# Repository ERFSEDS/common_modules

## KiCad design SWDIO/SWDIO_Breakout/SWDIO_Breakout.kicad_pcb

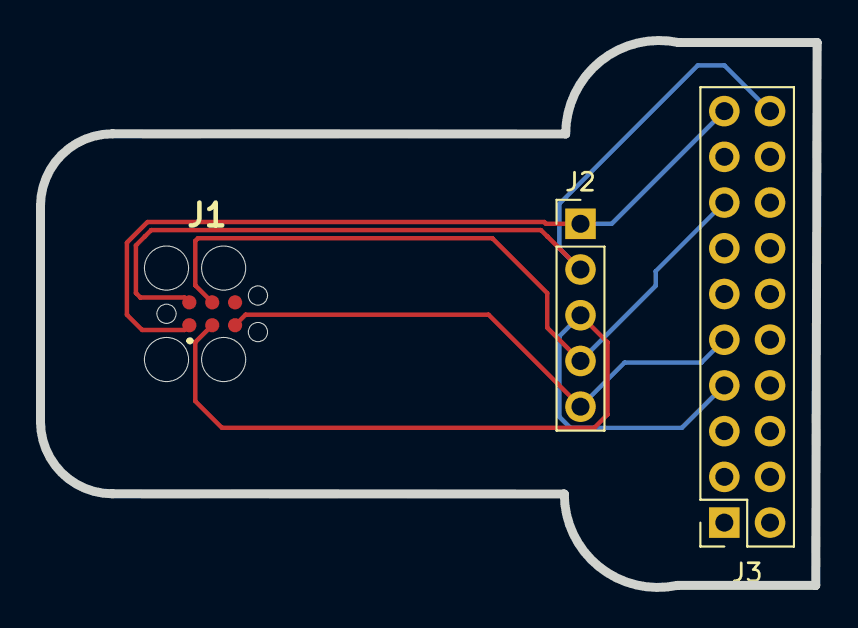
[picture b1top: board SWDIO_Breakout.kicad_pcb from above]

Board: 2 copper layers, 43.1 x 30.4 mm, 3 parts (0 on the bottom side), 5 nets.

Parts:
J1: 8.06.16; 80616
J2: Conn_01x05_Male; PinHeader_1x05_P2.54mm_Vertical
J3: Conn_01x20_Male; PinSocket_2x10_P2.54mm_Vertical

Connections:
+3.3V: J1.1, J2.1, J3.19
GND: J1.2, J2.2, J3.20
RESET: J1.4, J2.4, J3.15
SWCLK: J1.5, J2.5, J3.9
SWDIO: J1.3, J2.3, J3.7

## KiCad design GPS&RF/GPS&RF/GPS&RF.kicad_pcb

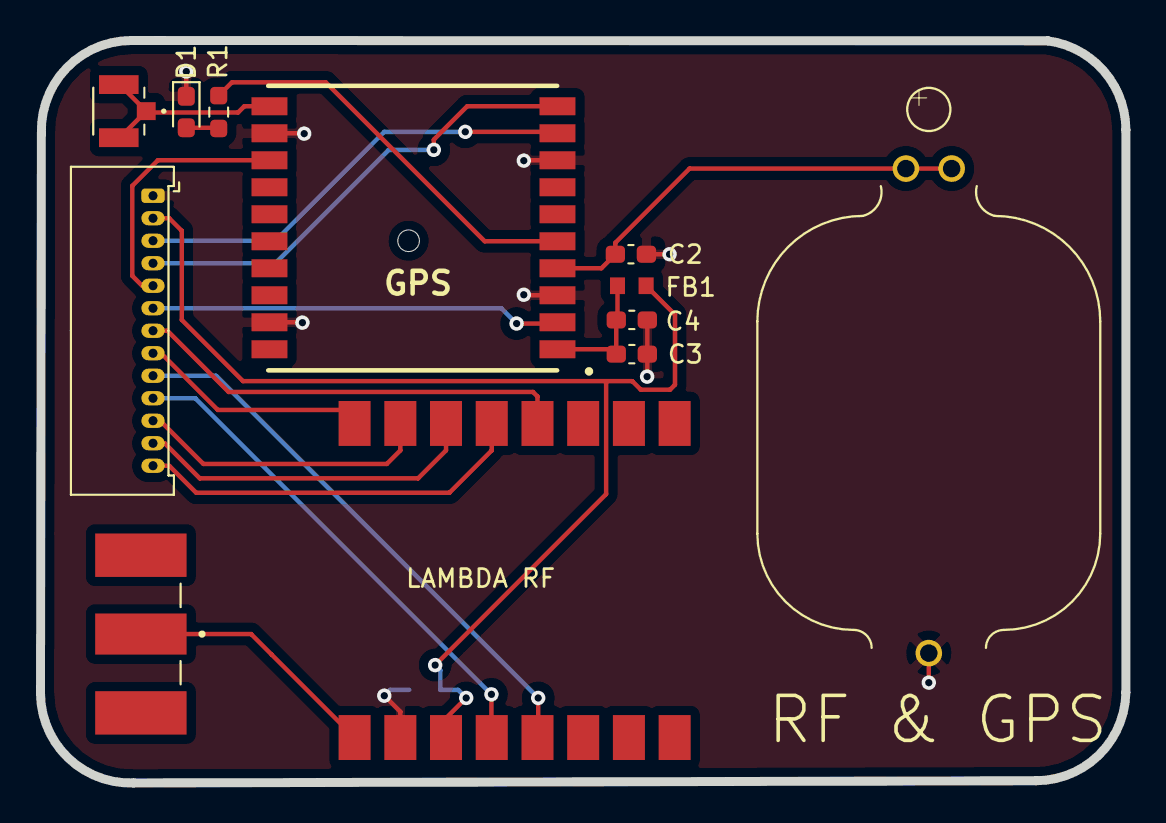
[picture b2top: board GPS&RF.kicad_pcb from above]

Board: 2 copper layers, 60.3 x 41.2 mm, 13 parts (1 on the bottom side), 19 nets.

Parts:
 : Conn_01x13_Male; Molex_PicoBlade_53048-1310_1x13_P1.25mm_Horizontal
 #2: U.FL-R-SMT(10); HRS_U.FL-R-SMT(10)
 #3: BATT; BAT_120591-1
 #4: Antenna; CINCH_142-0701-801
 LAMBDA RF: LAMBDA-9S-Global; LAMBDA-9S
C1: 100nF; C_0603_1608Metric_Pad1.08x0.95mm_HandSolder
C2, C3: 1uF; C_0603_1608Metric_Pad1.08x0.95mm_HandSolder
C4: 0.01uF; C_0603_1608Metric_Pad1.08x0.95mm_HandSolder
D1: LED; LED_0603_1608Metric_Pad1.05x0.95mm_HandSolder
FB1: Ferrite_Bead; BEADC1608X90N
GPS: FGPMMOPA6H
R1: 330ohm; R_0603_1608Metric_Pad0.98x0.95mm_HandSolder

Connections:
+3V3: .2, LAMBDA RF.3, C1.2, FB1.2
/1PPS: .5, GPS.13
/CS: .8, LAMBDA RF.16
/GPSRST: .6, GPS.2
/MISO: .12, LAMBDA RF.14
/MOSI: .11, LAMBDA RF.15
/RFRST: .7, LAMBDA RF.12
/RX_D1: .9, LAMBDA RF.5
/RX_D2: .3, GPS.9
/SCK: .13, LAMBDA RF.13
/TX_D1: .10, LAMBDA RF.4
/TX_D2: .4, GPS.10
GND: .1, #3.-, LAMBDA RF.2, C1.1, C2.2, C3.1, C4.1, D1.1, GPS.3, GPS.8, GPS.12, GPS.19
unnamed: #4.1, LAMBDA RF.1
unnamed: #3.+1, #3.+2, C2.1, GPS.4
unnamed: C3.2, C4.2, FB1.1, GPS.1
unnamed: D1.2, R1.2
unnamed: GPS.5, R1.1
unnamed: #2.1, #2.2, #2.3, GPS.11

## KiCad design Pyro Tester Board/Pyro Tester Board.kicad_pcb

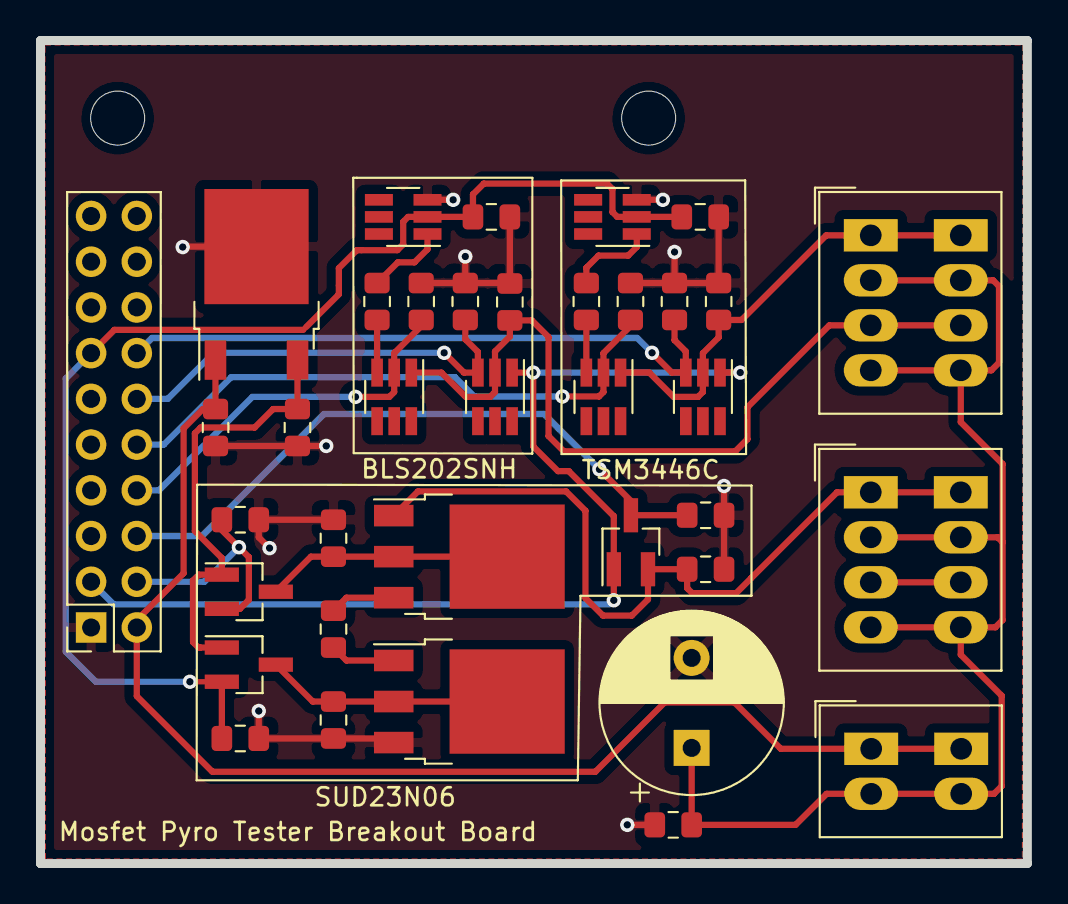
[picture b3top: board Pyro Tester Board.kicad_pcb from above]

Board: 2 copper layers, 54.8 x 45.7 mm, 39 parts (0 on the bottom side), 23 nets.

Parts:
C1: 1mF; CP_Radial_D10.0mm_P5.00mm
C2: 0.33uF; C_0805_2012Metric_Pad1.15x1.40mm_HandSolder
C3: 01.uF; C_0805_2012Metric_Pad1.15x1.40mm_HandSolder
H1, H2: MountingHole; MountingHole_3mm
J1: Conn_02x10_Counter_Clockwise; PinSocket_2x10_P2.54mm_Vertical
J2: Conn_01x02_Female; TerminalBlock_Phoenix_PTSM-0,5-2-2.5-H-THR_1x02_P2.50mm_Hor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
J3, J4: Conn_01x04_Female; TerminalBlock_Phoenix_PTSM-0,5-4-2.5-H-THR_1x04_P2.50mm_Hor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
Q1, Q2, Q3, Q4, Q5, Q6: Q_NJFET_DGS; SOT-23-6_Handsoldering
Q7, Q8, Q11: Q_NJFET_DGS; SOT-23_Handsoldering
Q9, Q10: Q_NJFET_DGS; TO-252-3_TabPin2
R1, R2, R3, R5, R6, R7, R9, R10, R11, R12, R13, R14, R16, R17, R18: 10k; R_0805_2012Metric_Pad1.15x1.40mm_HandSolder
R4, R8, R15: 3.3; R_0805_2012Metric_Pad1.15x1.40mm_HandSolder
U1: LM78M05_TO252; TO-252-2

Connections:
+3V3: J1.3, Q3.1, Q6.1, Q11.1
+5V: C3.1, Q7.1, Q8.1, U1.3
+BATT: C2.1, J1.2, J2.1, U1.1
/Arm: J1.13, Q2.2, Q5.2, Q8.2, R1.1, R12.1, R18.1
/Continuity1: J1.14, Q3.3, R10.1
/Continuity2: J1.12, Q6.3, R6.1
/Continuity3: J1.6, Q11.3, R17.1
/Fire1: J1.10, Q1.2, R7.1
/Fire2: J1.8, Q4.2, R3.1
/Fire3: J1.4, Q7.2, R11.1
/Pyro1: J3.1, Q1.1, Q3.2, R9.1
/Pyro2: J3.3, Q4.1, Q6.2, R5.1
/Pyro3: J4.1, Q9.1, Q11.2, R16.1
GND: C1.2, C2.2, C3.2, J1.1, Q2.3, Q5.3, Q10.3, R1.2, R2.2, R3.2, R5.2, R6.2, R7.2, R9.2, R10.2, R11.2, R12.2, R13.2, R14.2, R16.2, R17.2, R18.2, U1.2
unnamed: C1.1, J2.2, J3.2, J3.4, J4.2, J4.4, R2.1
unnamed: Q1.3, R8.1
unnamed: Q2.1, R8.2
unnamed: Q4.3, R4.1
unnamed: Q5.1, R4.2
unnamed: Q7.3, Q9.2, R13.1
unnamed: Q9.3, R15.1
unnamed: Q10.1, R15.2
unnamed: Q8.3, Q10.2, R14.1

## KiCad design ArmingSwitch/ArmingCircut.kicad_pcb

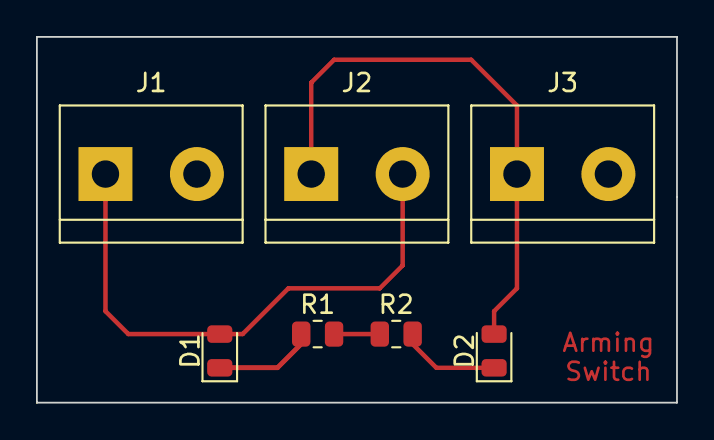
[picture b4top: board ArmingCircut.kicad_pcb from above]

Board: 2 copper layers, 35.6 x 20.3 mm, 7 parts (0 on the bottom side), 5 nets.

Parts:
D1, D2: LED; LED_0805_2012Metric
J1, J2, J3: Screw_Terminal_01x02; TerminalBlock_bornier-2_P5.08mm
R1, R2: R; R_0805_2012Metric

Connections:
GND: R1.2, R2.1
unnamed: D1.1, R1.1
unnamed: D1.2, J1.1, J2.2
unnamed: D2.1, R2.2
unnamed: D2.2, J2.1, J3.1

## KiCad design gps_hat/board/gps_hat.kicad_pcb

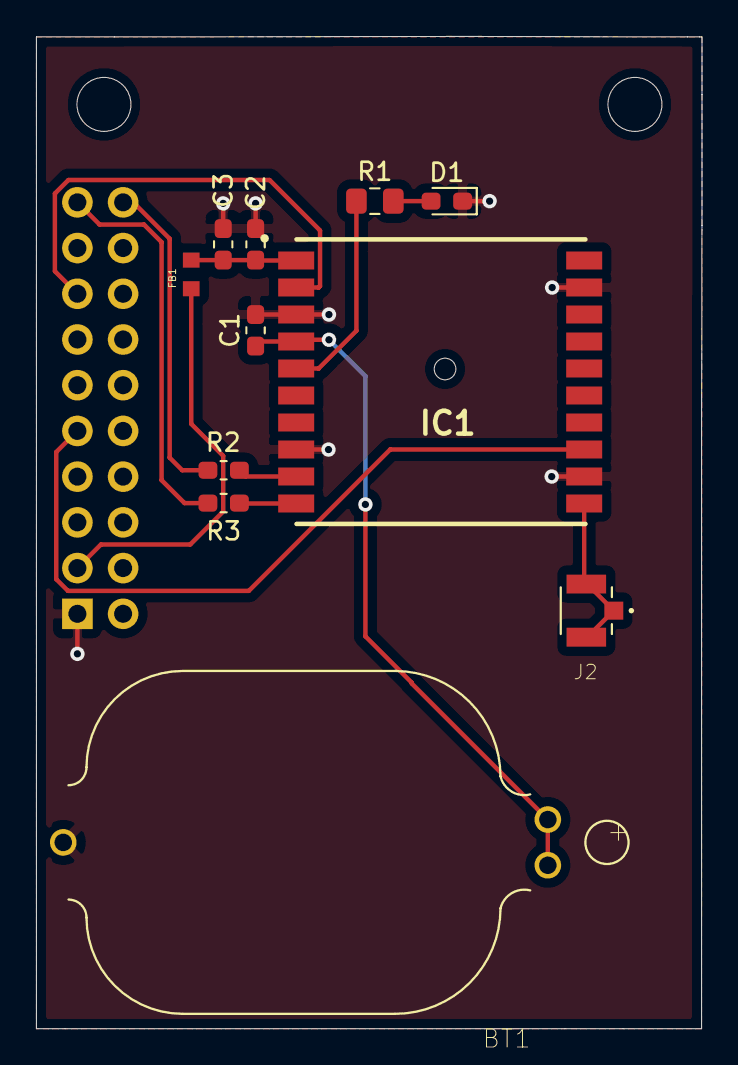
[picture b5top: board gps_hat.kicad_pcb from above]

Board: 2 copper layers, 37.0 x 55.1 mm, 14 parts (1 on the bottom side), 13 nets.

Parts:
 : MountingHole; MountingHole_3mm
 #2: MountingHole; MountingHole_3mm
BT1: BATT; BAT_120591-1
C1, C2: 1uF; C_0603_1608Metric_Pad1.05x0.95mm_HandSolder
C3: 0.01uF; C_0603_1608Metric_Pad1.05x0.95mm_HandSolder
D1: LED; LED_0603_1608Metric_Pad1.05x0.95mm_HandSolder
FB1: 600 Ohm; BEADC1608X90N
IC1: MTK3339; FGPMMOPA6H
J1: Conn_02x10_Odd_Even; PinHeader_2x10_P2.54mm_Vertical
J2: U.FL-R-SMT(10); HRS_U.FL-R-SMT(10)
R1: 330ohm; R_0805_2012Metric_Pad1.15x1.40mm_HandSolder
R2, R3: 330ohm; R_0603_1608Metric_Pad1.05x0.95mm_HandSolder

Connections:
+3V3: FB1.1, J1.3
/1PPS: IC1.13, J1.9
/NRESET: IC1.2, J1.15
/RX: J1.20, R2.2
/TX: J1.19, R3.2
GND: BT1.-, C1.2, C2.1, C3.1, D1.1, IC1.3, IC1.8, IC1.12, IC1.19, J1.1
unnamed: BT1.+1, BT1.+2, C1.1, IC1.4
unnamed: C2.2, C3.2, FB1.2, IC1.1
unnamed: D1.2, R1.2
unnamed: IC1.5, R1.1
unnamed: IC1.9, R2.1
unnamed: IC1.10, R3.1
unnamed: IC1.11, J2.1, J2.2, J2.3

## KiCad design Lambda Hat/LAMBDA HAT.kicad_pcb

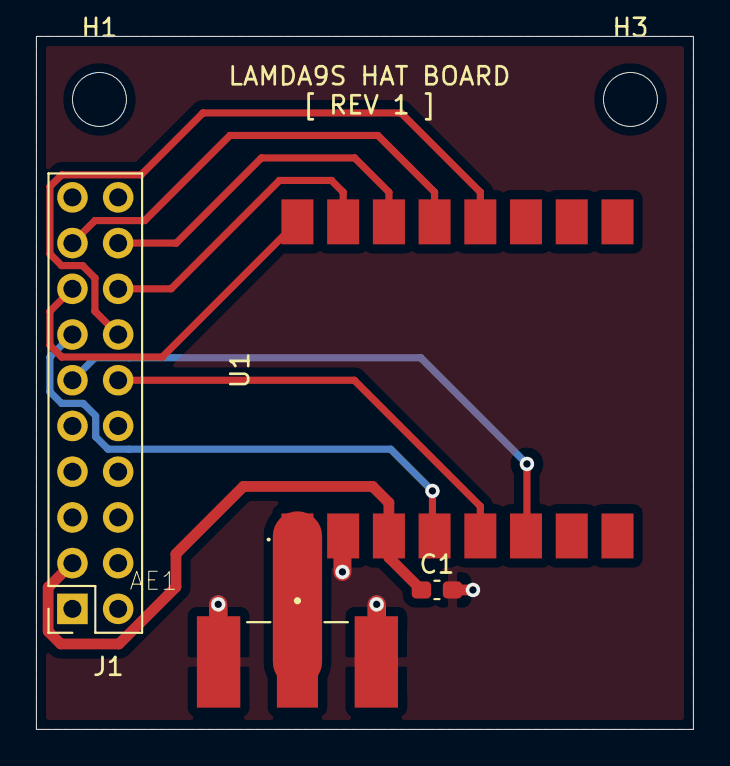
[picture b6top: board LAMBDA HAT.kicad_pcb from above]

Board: 2 copper layers, 36.5 x 38.5 mm, 6 parts (0 on the bottom side), 11 nets.

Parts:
AE1: Antenna; CINCH_142-0701-801
C1: 100n; C_0603_1608Metric_Pad1.08x0.95mm_HandSolder
H1, H3: MountingHole; MountingHole_3mm
J1: Conn_02x10_Counter_Clockwise; PinHeader_2x10_P2.54mm_Vertical
U1: LAMBDA-9S-Global; LAMBDA-9S

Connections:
+3V3: C1.1, J1.3, U1.3
/DIO: J1.11, U1.6
/MISO: J1.18, U1.14
/MOSI: J1.16, U1.15
/RESET: J1.14, U1.12
/RX_SWITCH: J1.13, U1.4
/SCK: J1.17, U1.13
/TX_SWITCH: J1.12, U1.5
/nCS: J1.15, U1.16
GND: AE1.S1, AE1.S2, AE1.S3, AE1.S4, C1.2, J1.1, U1.2
unnamed: AE1.1, U1.1

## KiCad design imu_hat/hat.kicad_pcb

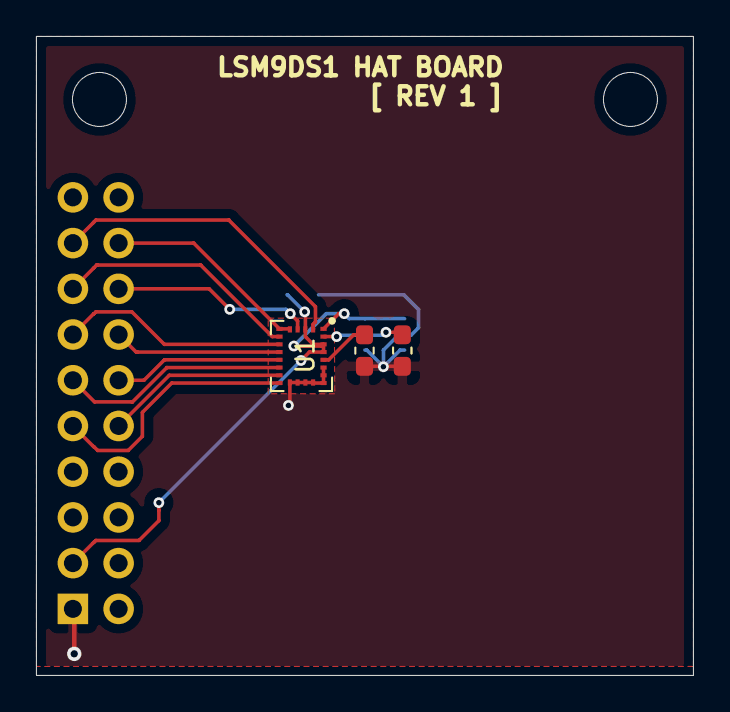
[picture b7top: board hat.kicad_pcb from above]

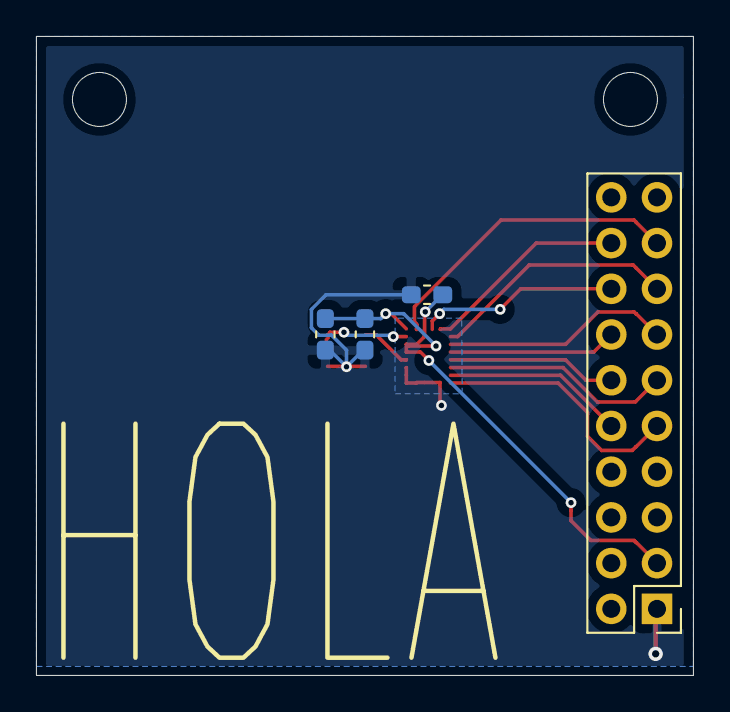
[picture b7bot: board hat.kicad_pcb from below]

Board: 2 copper layers, 36.5 x 35.5 mm, 9 parts (4 on the bottom side), 14 nets.

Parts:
C1: 10nF; C_0603_1608Metric_Pad1.05x0.95mm_HandSolder
C2, C3, C4: 100nF; C_0603_1608Metric_Pad1.05x0.95mm_HandSolder
C5: 10uF; C_0603_1608Metric_Pad1.05x0.95mm_HandSolder
H1, H3: MountingHole; MountingHole_3mm
J1: Conn_02x10_Odd_Even; PinHeader_2x10_P2.54mm_Vertical
U1: LSM9DS1; LGA-24L_3x3.5mm_P0.43mm

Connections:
+3V3: C2.1, C4.1, C5.1, J1.3, U1.1, U1.3, U1.22, U1.23
/CS: J1.15, U1.7
/CSM: J1.13, U1.8
/DEN: J1.9, U1.13
/DRDYM: J1.14, U1.9
/INT1: J1.11, U1.11
/INT2: J1.10, U1.12
/INTM: J1.12, U1.10
/MISO: J1.18, U1.5, U1.6
/MOSI: J1.16, U1.4
/SCLK: J1.17, U1.2
GND: C1.2, C2.2, C3.2, C4.2, C5.2, J1.1, U1.14, U1.15, U1.16, U1.17, U1.18, U1.19, U1.20
unnamed: C1.1, U1.21
unnamed: C3.1, U1.24

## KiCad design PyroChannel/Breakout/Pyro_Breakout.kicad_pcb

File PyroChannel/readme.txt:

This circuit is broken up into 2 sheets, an arming sheet, which each board
only needs one, then a pyro channel, which can have as many as desired
This circuit also allows for the pyro channel to be checked

The maximum voltage that this circuit can take is 12V, at which point the
transistors will break down. THe maximum current the transistors can
sustain is 5 amps continuous or 25 for a pulse

to fire a channel n
	digitalWrite(armPin, HIGH)
	digitalWite(channelNPin, HIGH)

to check if channel n is armed
	digitalRead(channelNPyro)

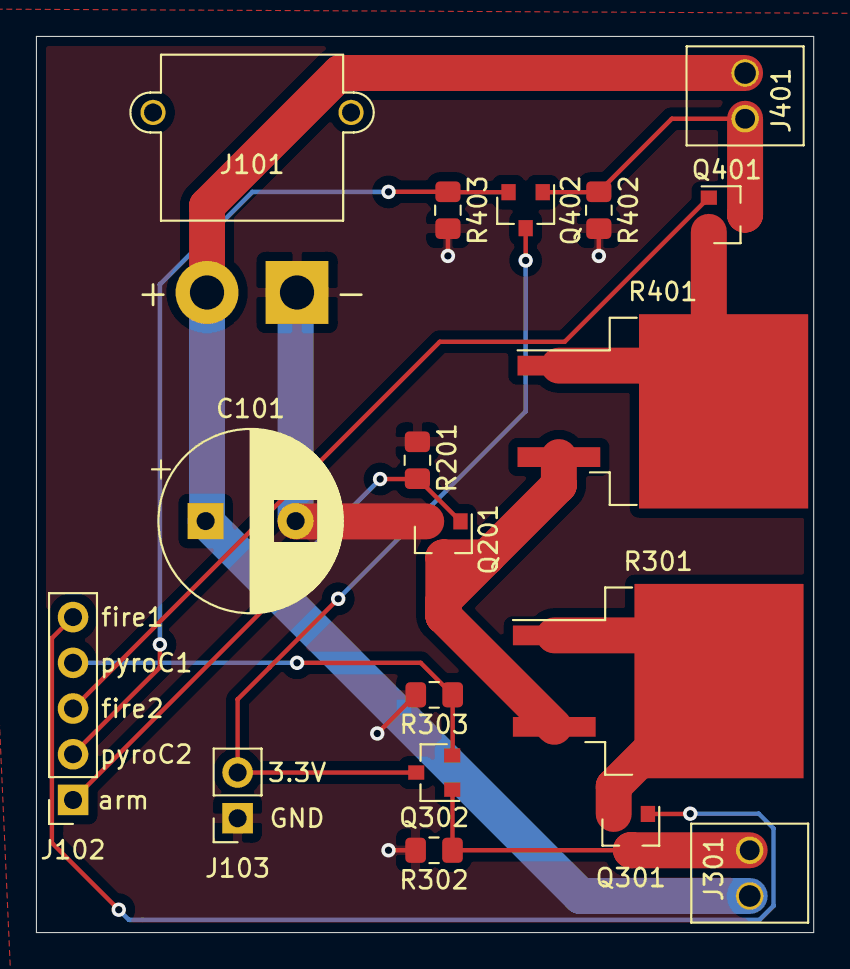
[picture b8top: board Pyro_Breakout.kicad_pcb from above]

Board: 2 copper layers, 43.2 x 49.8 mm, 18 parts (0 on the bottom side), 13 nets.

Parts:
C101: 1mF; CP_Radial_D10.0mm_P5.00mm
J101: Conn_01x02; AMASS_XT30PW-M_1x02_P2.50mm_Horizontal
J102: Conn_01x05; PinSocket_1x05_P2.54mm_Vertical
J103: Conn_01x02; PinSocket_1x02_P2.54mm_Vertical
J301, J401: Conn_01x02_Female; 2_pin_screw_terminal
Q201, Q301, Q302, Q401, Q402: IRLML6344TRPBFee; SOT-23
R201, R302, R303, R402, R403: 10k; R_0805_2012Metric_Pad1.15x1.40mm_HandSolder
R301, R401: 3.3; TO-263-2_TabPin1

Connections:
+3V3: J103.2, Q302.3, Q402.3
+BATT: C101.1, J101.2, J301.1, J401.1
/ArmSchematic/FireOut: Q201.3, R301.2, R401.2
/arm: J102.1, Q201.1, R201.1
/fire1: J102.5, Q301.1
/fire2: J102.3, Q401.1
/pyroCorrect1: J102.4, Q302.2, R303.1
/pyroCorrect2: J102.2, Q402.2, R403.1
GND: C101.2, J101.1, J103.1, Q201.2, R201.2, R302.2, R303.2, R402.2, R403.2
unnamed: J301.2, Q301.3, Q302.1, R302.1
unnamed: J401.2, Q401.3, Q402.1, R402.1
unnamed: Q301.2, R301.1
unnamed: Q401.2, R401.1

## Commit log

2020-06-02 Creating Structure
    Created a readme and gitignore
2020-06-02 Edited Readme
    Check before you commit
2020-06-02 Gyroscope breakout board
    Created the gyroscope board
2020-06-02 Restructured and reformatted to standards
    There was an unneccessary folder that I got rid of, also updated the project so that it follows the standards set out in the Cerberus Github GUide
2020-06-02 minor restructure
    moved the project into a sub-directory
2020-06-02 minor restructure
    Removed redundant layer
2020-06-02 removed redundant folder
    Two Common Modules folders
2020-06-02 Restored Git Ignore
    accidentally deleted it now I restored it
2020-06-02 Copied files to new repo
2020-06-02 Copied MCU files to new repo
2020-06-04 Added diodes. Clarified bootloader chip
2020-06-09 Barometer_Breakout Files
2020-06-09 Moved files to folder
2020-06-15 Deleted old Processor. Added STM with clocks and USB in progress
2020-06-16 Finalized USB with FTDI. Added caps and LED
2020-06-17 Added regulator and battery input and diode
2020-06-17 Cleaned up schematics. Added "filtering" page
2020-06-17 Added filtering caps
2020-06-18 Added pin headers and reset circuit. Need to change button footprint to something smaller
2020-06-20 Tied Boot0 to GND
2020-06-22 Finished rough schematic. Began routing clocks, USB, Reset, and battery circuits
2020-06-23 Finalized Schematic. Finished PCB routing. Needs silkscreen
2020-06-24 Finished Schematic and pcb. Ready for review.
2020-06-24 Updated schematic layout. Ready for review
2020-06-25 Final board design for review
2020-06-30 Adding Breakout board details for the accelerometer.
2020-07-01 Added Footprint and Symbol Libraries
2020-07-01 Minor Restructure. Added README
2020-07-01 Updated Readme. Requesting total review for completion of module.
2020-07-02 These are the files for the Flash and SD Breakout!
2020-07-02 I was a big dummy head no spaces for me!
2020-07-02 Fixed Minor Issues on schematic and layout
2020-07-02 Fixed Minor Issues. Added schematic template
2020-07-02 Fixed Minor issues
2020-07-02 Minor Silkscreen change. Added Signature. Final Approved Board
2020-07-03 Post review fix. Added title to title block
2020-07-03 Added Readme
2020-07-03 Updated post review
2020-07-03 Minor routing fix
2020-07-03 Added datasheet for processor. Post-Review
2020-07-04 Found capacitor issue. Switched C909 to ceramic. Post-review
2020-07-05 Fixed Barometer Files
    It looks all nice a pretty now and sorta organized
2020-07-05 Board Additions
    Added the ground pour on bottom layer. Added no connect symbol on 4th pin. Added silk screen for pin outs
2020-07-06 Updated Flash SD Board Files
    Refined Files
2020-07-06 Fixed Minor Issues
    BOOM!
2020-07-07 Fixed even more issues
    Hopefully the last fixes
2020-07-07 Barometer Folder Fix
2020-07-07 Power Flags are Stupid
2020-07-13 First Draft of Power Supply
    Took long enough
2020-07-13 Fixed the Silk Screen
    Looks all pretty now
2020-07-14 Updated Pseudo Code for Flash & SD
    Added some general structure and basic work through
2020-07-14 Combined symbol libraries
2020-07-14 Updated version (v3) with all the issues pointed out by Charles fixed
2020-07-16 Fixed tracing
2020-07-18 Created Pyro Circuit
2020-07-23 Temp commit for pyro change
2020-07-23 Forgot to save first :/
2020-07-23 Updated Heirarchichal schematics and breakout to fix checkPyro error
2020-07-23 Created Gyroscope heirachical schematic
2020-07-27 Matthew you forgot to connect a pin :(
2020-07-28 Fixed Diode Thingy
2020-07-28 Minor Silkscreen Change
2020-07-28 Added pull down to Arming mosfet on pyro channel
2020-07-28 Minor change
2020-07-29 Minor Change in value on Crystal Caps
2020-07-30 adjusted gyro soldermask
2020-08-01 Cleaned up the Footprint Libraries
    Barometer, FHSD, and Power Supply
2020-08-06 Fixed Symbol Stuff
2020-10-14 Fixed the symbols from schematic
2020-10-17 Update Symbols & Footprints for Capacitors
    Did not change Pyro ones!
2020-10-21 Added Pull Downs to Pyro & Diodes for Power supply
    Other changes such as annotation and footprint shrink also took place
2020-10-21 Fixed Broken Directories for Footprint Libraries
2020-10-22 Started some routing and removed a diode for 5v which wasn't in use
2020-10-24 Simple Change
2020-10-25 Stage Bruh
2020-10-25 Good Change
2020-11-02 Routing and Minor Fixes
2020-11-08 Matts changes all at once, why did this not commit
2020-11-12 Changes with Final Nova
2021-01-20 RF HAT
    Lambda hat
2021-02-01 Edited IMU
2021-02-01 Made New Dimensions
2021-02-05 Shorted PCB
2021-02-08 Updated the GPS .sch file > needs work
2021-02-08 Made Files Look Pretty :)
2021-02-08 Messed UPPP
2021-02-08 Made Files Pretty
2021-02-09 add hi to readme
2021-02-10 Pushing new rev 2 branch
2021-02-10 Staging For Nova Rev 2
2021-02-10 Staged for Rev 2 progress push
2021-02-11 Removing IMU from GPS branch
2021-02-11 Moved IMU files
2021-02-15 The hopefully fixed RF board from David
2021-02-16 Fixed global issues
2021-02-17 Minor Changes
2021-02-18 MORE
2021-02-18 CHANGER
2021-02-22 yuhhh
2021-02-22 dumb system
2021-02-22 Possibly Fixed Footprint Issue
2021-02-24 yikes
2021-02-27 Edited GPU_HAT
2021-02-28 Finished GPU_HAT
2021-02-28 Last Revision
2021-03-02 coolio
2021-03-02 Changes to Misc
2021-03-02 Added footprints
2021-03-03 updated USB
2021-03-03 Modified pyro footprints
2021-03-03 Micro Sd fix
2021-03-03 Fixed PCB Layout
2021-03-04 Fixed GPS GND
2021-03-04 USB C Thingy
2021-03-06 Added Datasheets and Orderlinks
    I also updated the U.FL connector so that it is closer and easier to solder onto the PCB
2021-03-06 Fixed symbols
2021-03-08 Fixed GitIgnore file
2021-03-30 Made SCH for GPS and RF hat
2021-05-29 stuff
2021-08-06 &RF: Auto stash before checking out "origin/keepchanges"
2021-08-06 Part of the Minor Changes to Rev 2
2021-08-16 Updated Rev 2 Board August RF/GPS Fix
2021-08-21 Finished the GPS&RF schematic
    Replaced the 8 pin conn with a 13 pin conn_molex_PicoBlade
2021-08-22 Finished SCH and PCB
    Finished everything, might need to edit a few things but pushing the 'final' now
2021-09-05 COMPLETED RF&GPS BOARD!
    hoooorahhhh
2021-09-21 Created and Finished SWDIO breakout
2021-09-29 Arming Switch
2021-09-29 moved components around
2021-09-29 traces look cooler, imo
2021-09-29 added text
2021-09-30 text
2021-09-30 added screw terminals
2021-09-30 no more errors!
2021-10-02 Rev 2 Changes for update
2021-10-02 Made Pyro Tester Breakout
2021-10-03 Further Updates for Rev 2 Revision
2021-10-03 Fixed up the Silkscreen layer
2021-10-13 added 20 pin for testing/backup
2021-10-20 RF Breakout
2021-10-27 Changes to Pyro Logic Circuit
2021-10-27 Updated Filtering for MCU
2021-10-29 Changes for Rev 2 PCB Layout
2021-11-03 Finished Display
2021-11-16 Entered datasheet
2022-01-23 Added U8 footprint and edited pads
2022-01-23 Added 2 INT
2022-01-26 Created GBR .zip file
2022-03-04 Added 6 pin SWDIO breakout from rev1
2022-03-04 Updated schematic files to new kicad version
2022-03-04 Renamed SWD to remove space from name
